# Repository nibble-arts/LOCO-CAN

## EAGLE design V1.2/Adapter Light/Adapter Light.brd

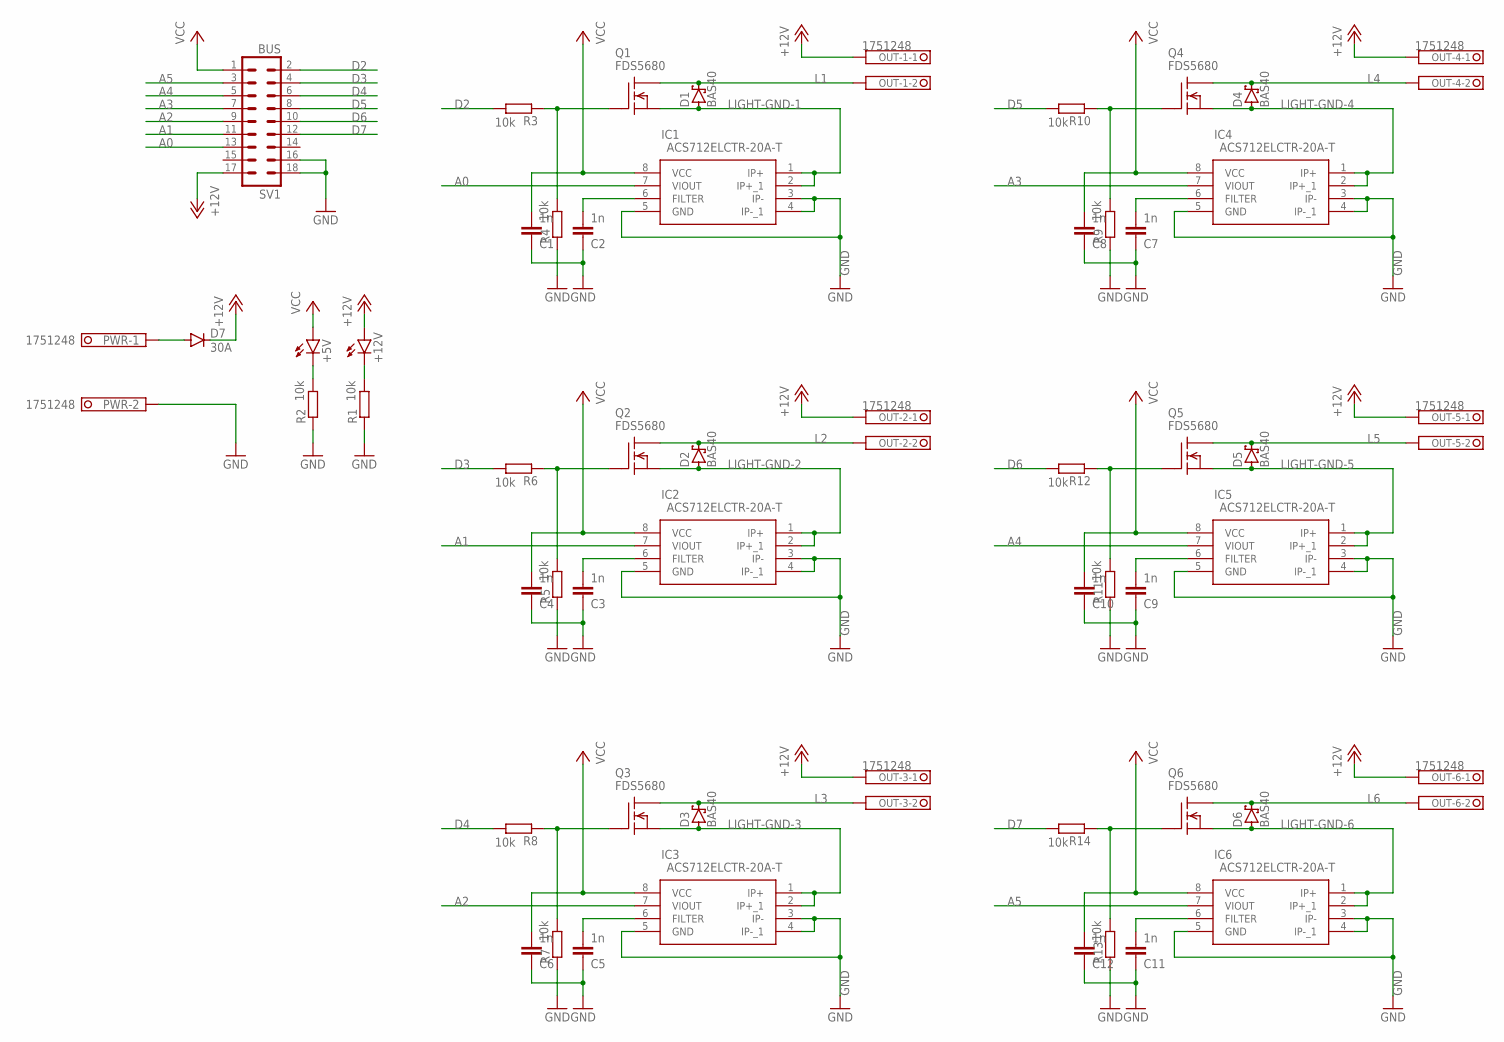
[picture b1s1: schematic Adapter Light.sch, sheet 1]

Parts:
+5V, +12V: LED3MM
C1, C2, C3, C4, C5, C6, C7, C8, C9, C10, C11, C12: 1n; C0402K
D1, D2, D3, D4, D5, D6: BAS40; SOT23
D7: 30A; DO15-12
IC1, IC2, IC3, IC4, IC5, IC6: ACS712ELCTR-20A-T; SOIC127P600X175-8N
OUT-1, OUT-2, OUT-3, OUT-4, OUT-5, OUT-6: 1751248
PWR: 1751248
Q1, Q2, Q3, Q4, Q5, Q6: FDS5680; SO-8
R1, R2, R3, R4, R5, R6, R7, R8, R9, R10, R11, R12, R13, R14: 10k; MINI_MELF-0102W
SV1: BUS; MA09-2

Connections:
+12V: +12V.A, D7.C, OUT-1.1, OUT-2.1, OUT-3.1, OUT-4.1, OUT-5.1, OUT-6.1, SV1.17
A0: IC1.7 (VIOUT), SV1.13
A1: IC2.7 (VIOUT), SV1.11
A2: IC3.7 (VIOUT), SV1.9
A3: IC4.7 (VIOUT), SV1.7
A4: IC5.7 (VIOUT), SV1.5
A5: IC6.7 (VIOUT), SV1.3
D2: R3.2, SV1.2
D3: R6.2, SV1.4
D4: R8.2, SV1.6
D5: R10.2, SV1.8
D6: R12.2, SV1.10
D7: R14.2, SV1.12
GND: C1.1, C2.1, C3.1, C4.1, C5.1, C6.1, C7.1, C8.1, C9.1, C10.1, C11.1, C12.1, IC1.3 (IP-), IC1.4 (IP-_1), IC1.5 (GND), IC2.3 (IP-), IC2.4 (IP-_1), IC2.5 (GND), IC3.3 (IP-), IC3.4 (IP-_1), IC3.5 (GND), IC4.3 (IP-), IC4.4 (IP-_1), IC4.5 (GND), IC5.3 (IP-), IC5.4 (IP-_1), IC5.5 (GND), IC6.3 (IP-), IC6.4 (IP-_1), IC6.5 (GND), PWR.2, R1.1, R2.1, R4.1, R5.1, R7.1, R9.1, R11.1, R13.1, SV1.16, SV1.18
L1: D1.3 (C), OUT-1.2, Q1.5 (D), Q1.6 (D), Q1.7 (D), Q1.8 (D)
L2: D2.3 (C), OUT-2.2, Q2.5 (D), Q2.6 (D), Q2.7 (D), Q2.8 (D)
L3: D3.3 (C), OUT-3.2, Q3.5 (D), Q3.6 (D), Q3.7 (D), Q3.8 (D)
L4: D4.3 (C), OUT-4.2, Q4.5 (D), Q4.6 (D), Q4.7 (D), Q4.8 (D)
L5: D5.3 (C), OUT-5.2, Q5.5 (D), Q5.6 (D), Q5.7 (D), Q5.8 (D)
L6: D6.3 (C), OUT-6.2, Q6.5 (D), Q6.6 (D), Q6.7 (D), Q6.8 (D)
LIGHT-GND-1: D1.1 (A), IC1.1 (IP+), IC1.2 (IP+_1), Q1.1 (S), Q1.2 (S), Q1.3 (S)
LIGHT-GND-2: D2.1 (A), IC2.1 (IP+), IC2.2 (IP+_1), Q2.1 (S), Q2.2 (S), Q2.3 (S)
LIGHT-GND-3: D3.1 (A), IC3.1 (IP+), IC3.2 (IP+_1), Q3.1 (S), Q3.2 (S), Q3.3 (S)
LIGHT-GND-4: D4.1 (A), IC4.1 (IP+), IC4.2 (IP+_1), Q4.1 (S), Q4.2 (S), Q4.3 (S)
LIGHT-GND-5: D5.1 (A), IC5.1 (IP+), IC5.2 (IP+_1), Q5.1 (S), Q5.2 (S), Q5.3 (S)
LIGHT-GND-6: D6.1 (A), IC6.1 (IP+), IC6.2 (IP+_1), Q6.1 (S), Q6.2 (S), Q6.3 (S)
unnamed: C2.2, IC1.6 (FILTER)
unnamed: C3.2, IC2.6 (FILTER)
unnamed: Q2.4 (G), R5.2, R6.1
unnamed: C5.2, IC3.6 (FILTER)
unnamed: Q3.4 (G), R7.2, R8.1
unnamed: +12V.K (C), R1.2
unnamed: C7.2, IC4.6 (FILTER)
unnamed: Q4.4 (G), R9.2, R10.1
unnamed: Q1.4 (G), R3.1, R4.2
unnamed: C9.2, IC5.6 (FILTER)
unnamed: Q5.4 (G), R11.2, R12.1
unnamed: +5V.K (C), R2.2
unnamed: C11.2, IC6.6 (FILTER)
unnamed: Q6.4 (G), R13.2, R14.1
unnamed: D7.A, PWR.1
VCC: +5V.A, C1.2, C4.2, C6.2, C8.2, C10.2, C12.2, IC1.8 (VCC), IC2.8 (VCC), IC3.8 (VCC), IC4.8 (VCC), IC5.8 (VCC), IC6.8 (VCC), SV1.1

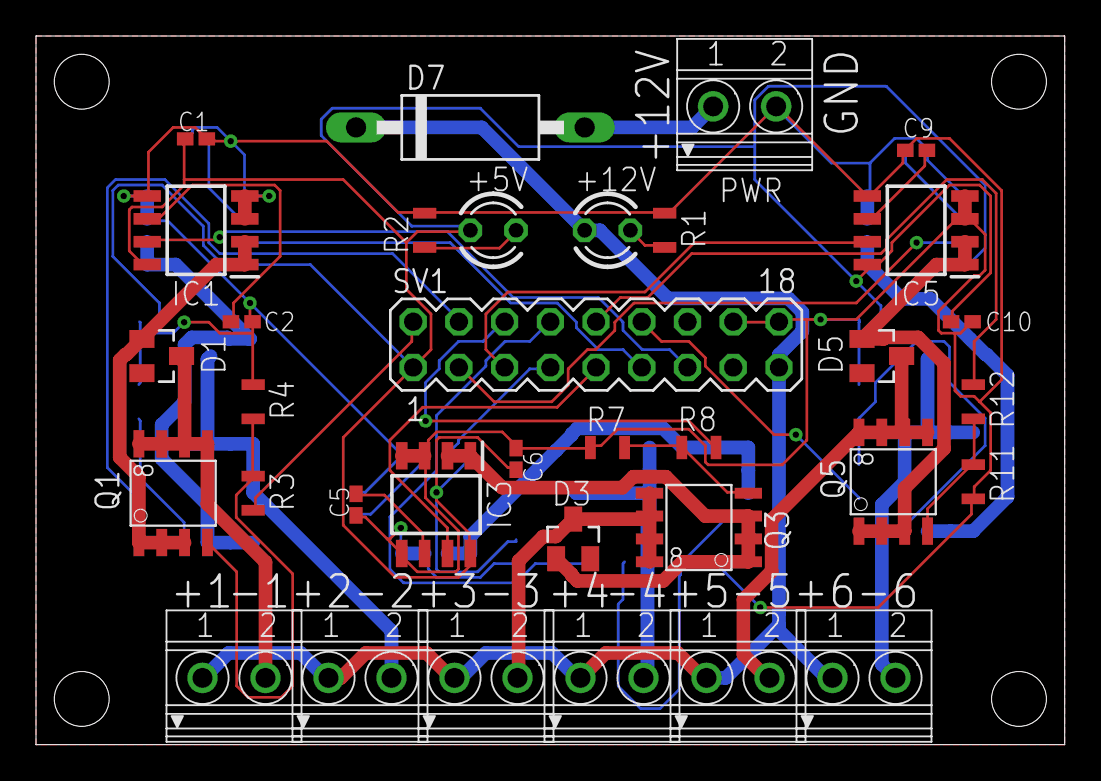
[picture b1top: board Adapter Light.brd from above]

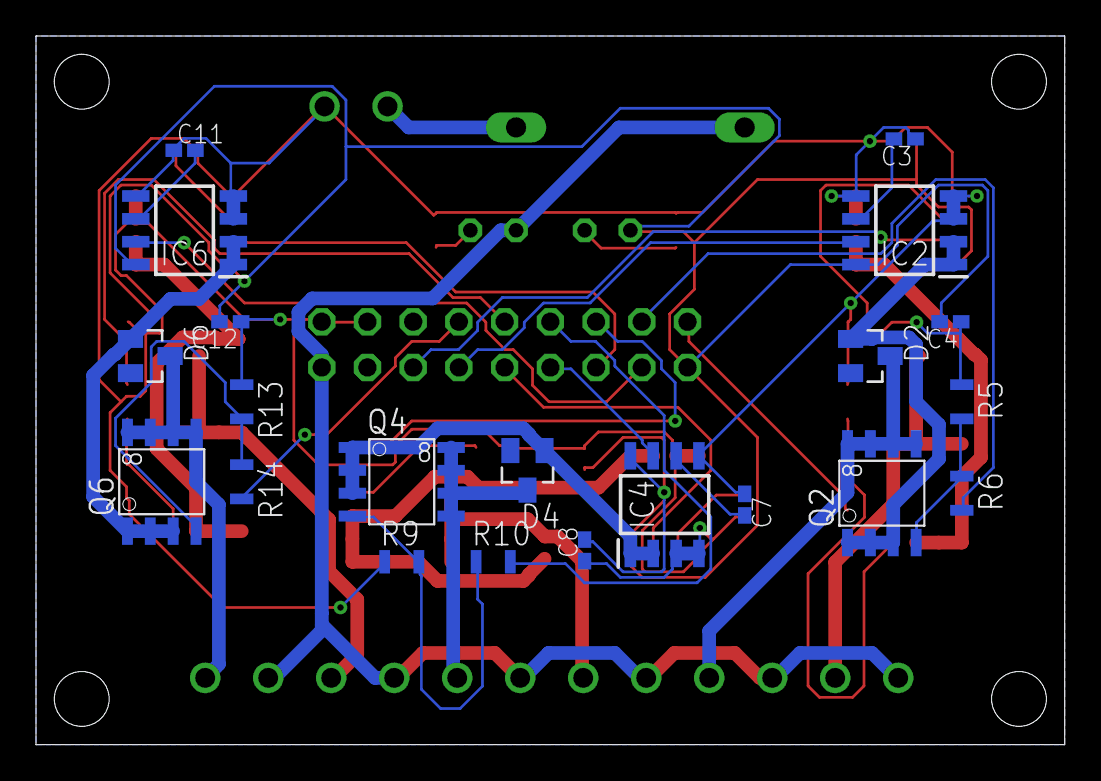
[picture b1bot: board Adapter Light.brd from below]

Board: 2 copper layers, 57.1 x 39.4 mm, 55 parts (21 on the bottom side), 42 nets.

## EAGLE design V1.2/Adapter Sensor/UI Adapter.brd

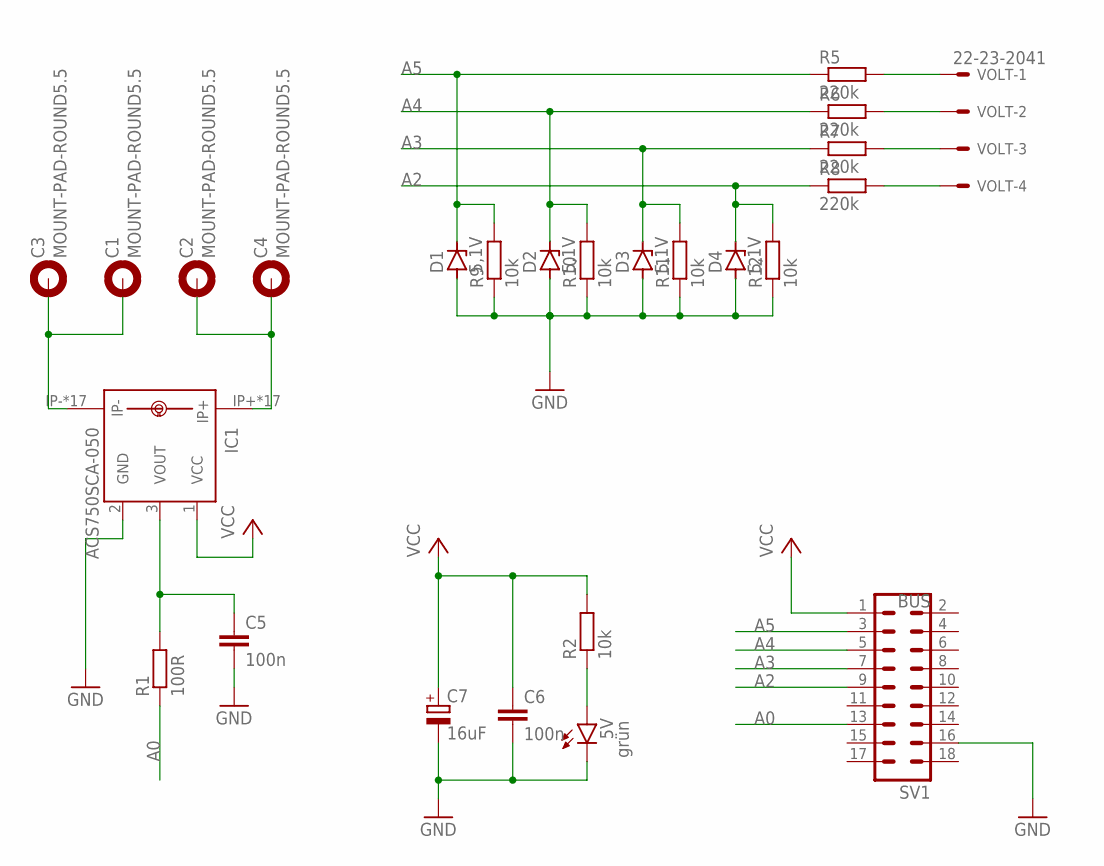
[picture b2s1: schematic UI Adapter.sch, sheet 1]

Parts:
5V: grün; LED3MM
C1, C2, C3, C4: MOUNT-PAD-ROUND5.5; 5,5-PAD
C5, C6: 100n; C025-024X044
C7: 16uF; E2-5
D1, D2, D3, D4: 5,1V; ZDIO-7.5
IC1: ACS750SCA-050; ACS75050
R1: 100R; 0204V
R2, R9, R10, R11, R12: 10k; 0204V
R5, R6, R7, R8: 220k; 0204V
SV1: BUS; MA09-2
VOLT: 22-23-2041

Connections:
A0: R1.1, SV1.13
A2: D4.C, R8.1, R12.2, SV1.9
A3: D3.C, R7.1, R11.2, SV1.7
A4: D2.C, R6.1, R10.2, SV1.5
A5: D1.C, R5.1, R9.2, SV1.3
C1: C1.B5,5, C3.B5,5, IC1.IP-, IC1.IP-@2 (IP-), IC1.IP-@3 (IP-), IC1.IP-@4 (IP-), IC1.IP-@5 (IP-), IC1.IP-@6 (IP-), IC1.IP-@7 (IP-), IC1.IP-@8 (IP-), IC1.IP-@9 (IP-), IC1.IP-@10 (IP-), IC1.IP-@11 (IP-), IC1.IP-@12 (IP-), IC1.IP-@13 (IP-), IC1.IP-@14 (IP-), IC1.IP-@15 (IP-), IC1.IP-@16 (IP-), IC1.IP-@17 (IP-)
C2: C2.B5,5, C4.B5,5, IC1.IP+, IC1.IP+@2 (IP+), IC1.IP+@3 (IP+), IC1.IP+@4 (IP+), IC1.IP+@5 (IP+), IC1.IP+@6 (IP+), IC1.IP+@7 (IP+), IC1.IP+@8 (IP+), IC1.IP+@9 (IP+), IC1.IP+@10 (IP+), IC1.IP+@11 (IP+), IC1.IP+@12 (IP+), IC1.IP+@13 (IP+), IC1.IP+@14 (IP+), IC1.IP+@15 (IP+), IC1.IP+@16 (IP+), IC1.IP+@17 (IP+)
GND: 5V.K (C), C5.2, C6.2, C7.-, D1.A, D2.A, D3.A, D4.A, IC1.2 (GND), R9.1, R10.1, R11.1, R12.1, SV1.16
unnamed: 5V.A, R2.1
unnamed: C5.1, IC1.3 (VOUT), R1.2
unnamed: R5.2, VOLT.1
unnamed: R6.2, VOLT.2
unnamed: R7.2, VOLT.3
unnamed: R8.2, VOLT.4
VCC: C6.1, C7.+, IC1.1 (VCC), R2.2, SV1.1

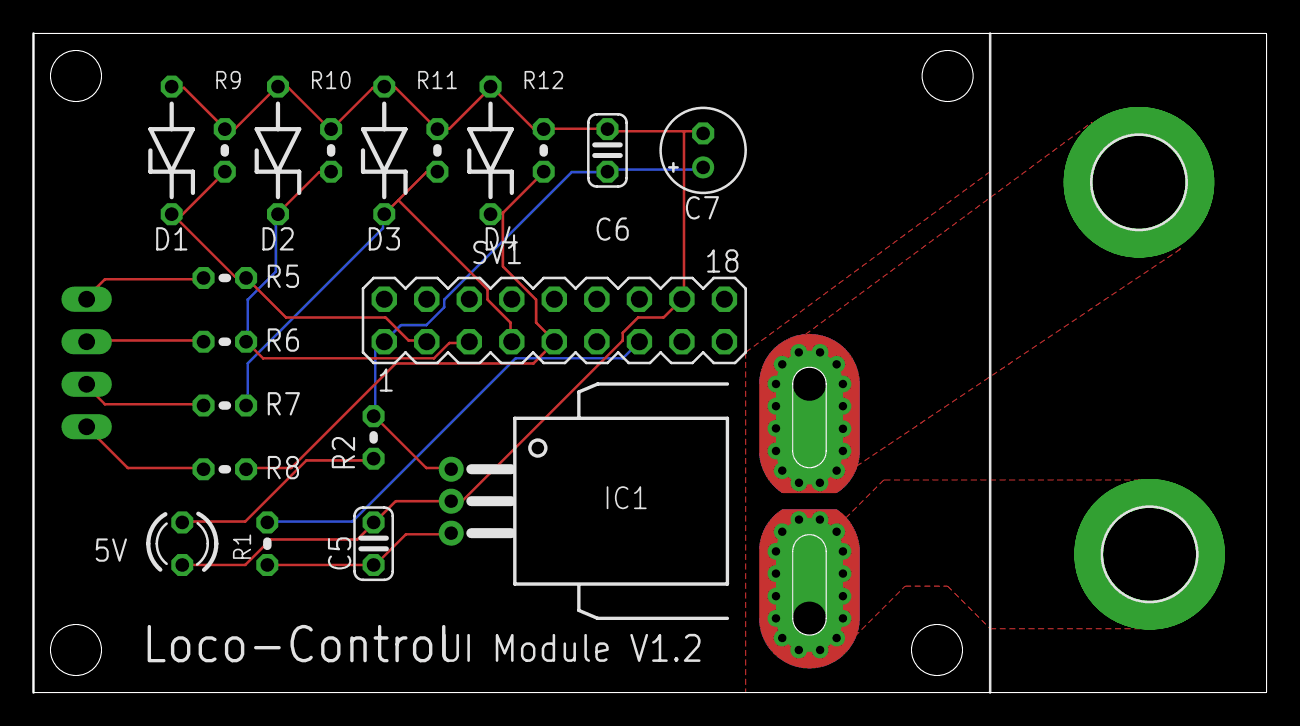
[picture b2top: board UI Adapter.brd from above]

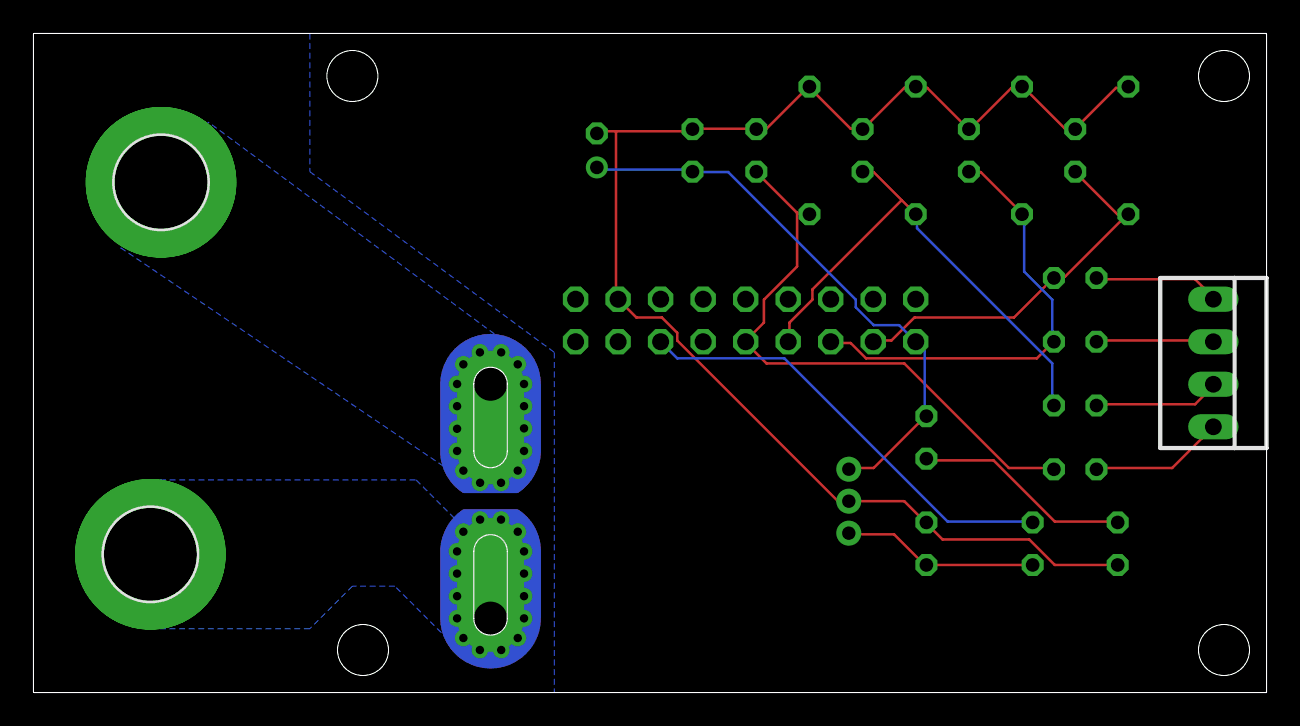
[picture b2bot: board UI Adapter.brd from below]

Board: 2 copper layers, 73.7 x 39.4 mm, 25 parts (3 on the bottom side), 15 nets.

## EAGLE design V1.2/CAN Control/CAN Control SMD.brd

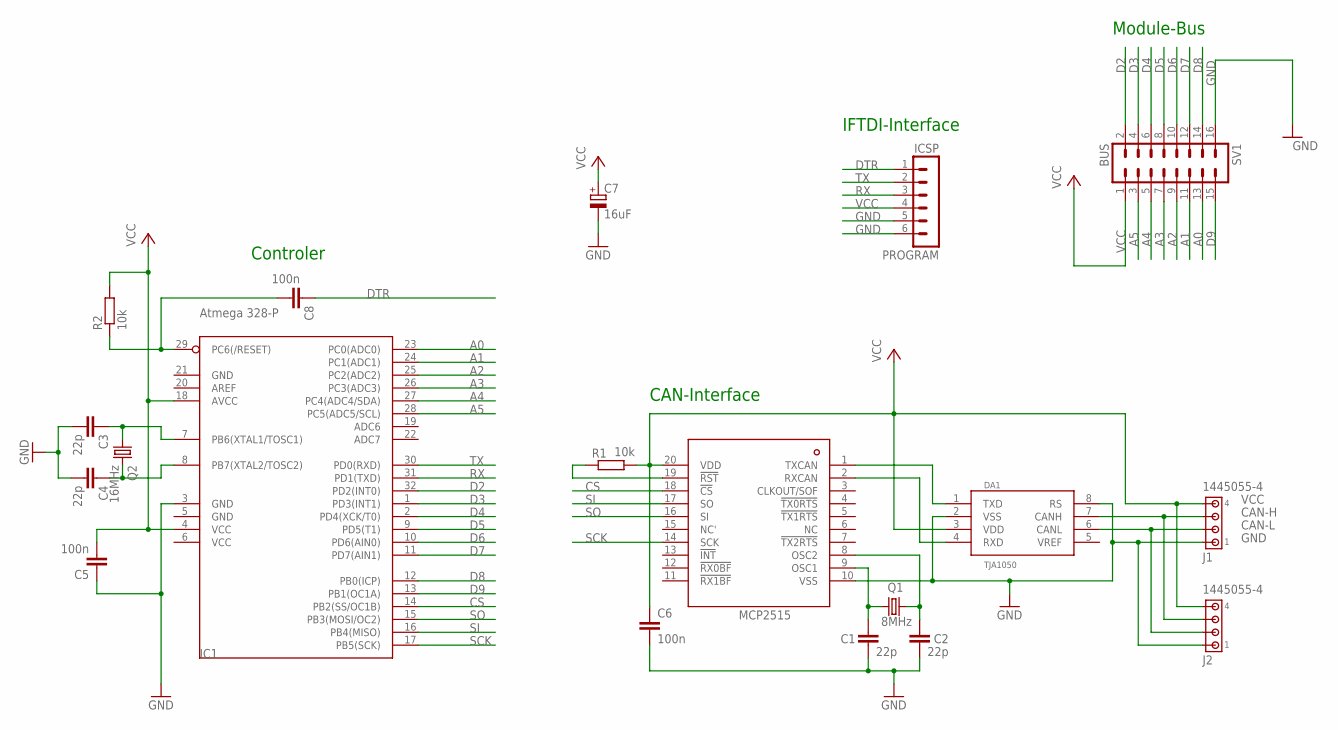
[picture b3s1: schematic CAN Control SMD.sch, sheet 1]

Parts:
C1, C2, C3, C4: 22p; C0402K
C5, C6, C8: 100n; C0402K
C7: 16uF; A/3216-18W
DA1: TJA1050; SO08
IC1: Atmega 328-P; TQFP32-08
IC2: MCP2515; TSSOP20
J1, J2: 1445055-4
PROGRAM: ICSP; MA06-1
Q1: 8MHz; HC49/S
Q2: 16MHz; HC49/S
R1, R2: 10k; MINI_MELF-0102W
SV1: BUS; MA08-2

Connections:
A0: IC1.23 (PC0(ADC0)), SV1.13
A1: IC1.24 (PC1(ADC1)), SV1.11
A2: IC1.25 (PC2(ADC2)), SV1.9
A3: IC1.26 (PC3(ADC3)), SV1.7
A4: IC1.27 (PC4(ADC4/SDA)), SV1.5
A5: IC1.28 (PC5(ADC5/SCL)), SV1.3
CAN-H: DA1.7 (CANH), J1.3, J2.3
CAN-L: DA1.6 (CANL), J1.2, J2.2
CAN-OCC1: C1.1, IC2.9 (OSC1), Q1.1
CAN-OCC2: C2.1, IC2.8 (OSC2), Q1.2
CS: IC1.14 (PB2(SS/OC1B)), IC2.18 (!CS)
D2: IC1.32 (PD2(INT0)), SV1.2
D3: IC1.1 (PD3(INT1)), SV1.4
D4: IC1.2 (PD4(XCK/T0)), SV1.6
D5: IC1.9 (PD5(T1)), SV1.8
D6: IC1.10 (PD6(AIN0)), SV1.10
D7: IC1.11 (PD7(AIN1)), SV1.12
D8: IC1.12 (PB0(ICP)), SV1.14
D9: IC1.13 (PB1(OC1A)), SV1.15
DTR: C8.1, PROGRAM.1
GND: C1.2, C2.2, C3.2, C4.2, C5.1, C6.2, C7.-, DA1.2 (VSS), DA1.8 (RS), IC1.3 (GND), IC1.5 (GND), IC1.21 (GND), IC2.10 (VSS), J1.1, J2.1, PROGRAM.5, PROGRAM.6, SV1.16
unnamed: IC2.19 (!RST), R1.1
unnamed: C3.1, IC1.7 (PB6(XTAL1/TOSC1)), Q2.1
unnamed: C4.1, IC1.8 (PB7(XTAL2/TOSC2)), Q2.2
unnamed: C8.2, IC1.29 (PC6(/RESET)), R2.1
RX: IC1.31 (PD1(TXD)), PROGRAM.3
RXCAN: DA1.4 (RXD), IC2.2 (RXCAN)
SCK: IC1.17 (PB5(SCK)), IC2.14 (SCK)
SI: IC1.16 (PB4(MISO)), IC2.17 (SO)
SO: IC1.15 (PB3(MOSI/OC2)), IC2.16 (SI)
TX: IC1.30 (PD0(RXD)), PROGRAM.2
TXCAN: DA1.1 (TXD), IC2.1 (TXCAN)
VCC: C5.2, C6.1, C7.+, DA1.3 (VDD), IC1.4 (VCC), IC1.6 (VCC), IC1.18 (AVCC), IC2.20 (VDD), J1.4, J2.4, PROGRAM.4, R1.2, R2.2, SV1.1

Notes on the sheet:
Module-Bus
IFTDI-Interface
CAN-Interface
Controler

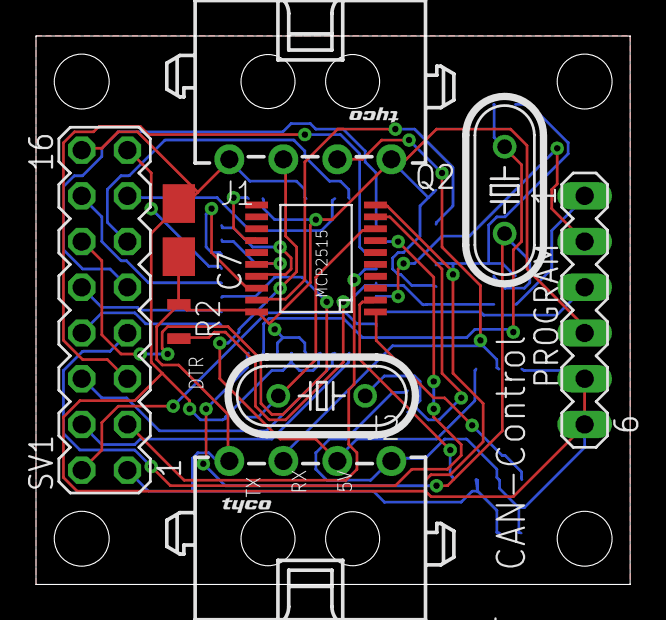
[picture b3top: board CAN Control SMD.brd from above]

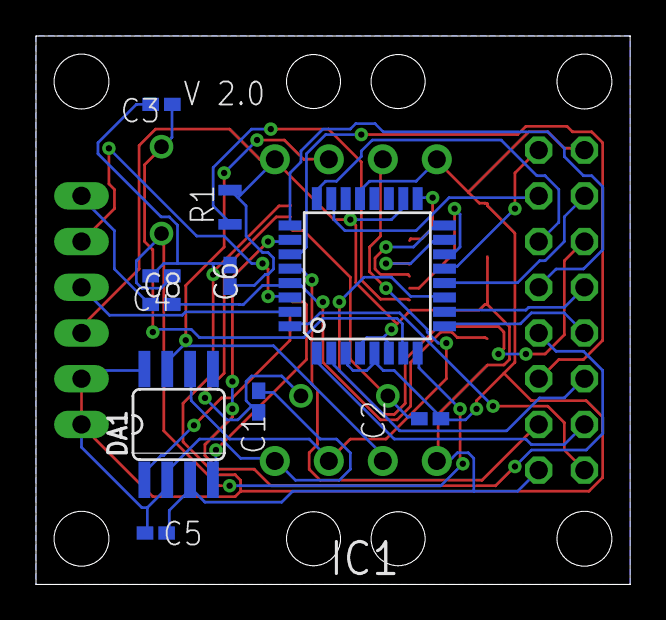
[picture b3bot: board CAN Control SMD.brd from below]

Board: 2 copper layers, 33.0 x 30.5 mm, 19 parts (10 on the bottom side), 33 nets.

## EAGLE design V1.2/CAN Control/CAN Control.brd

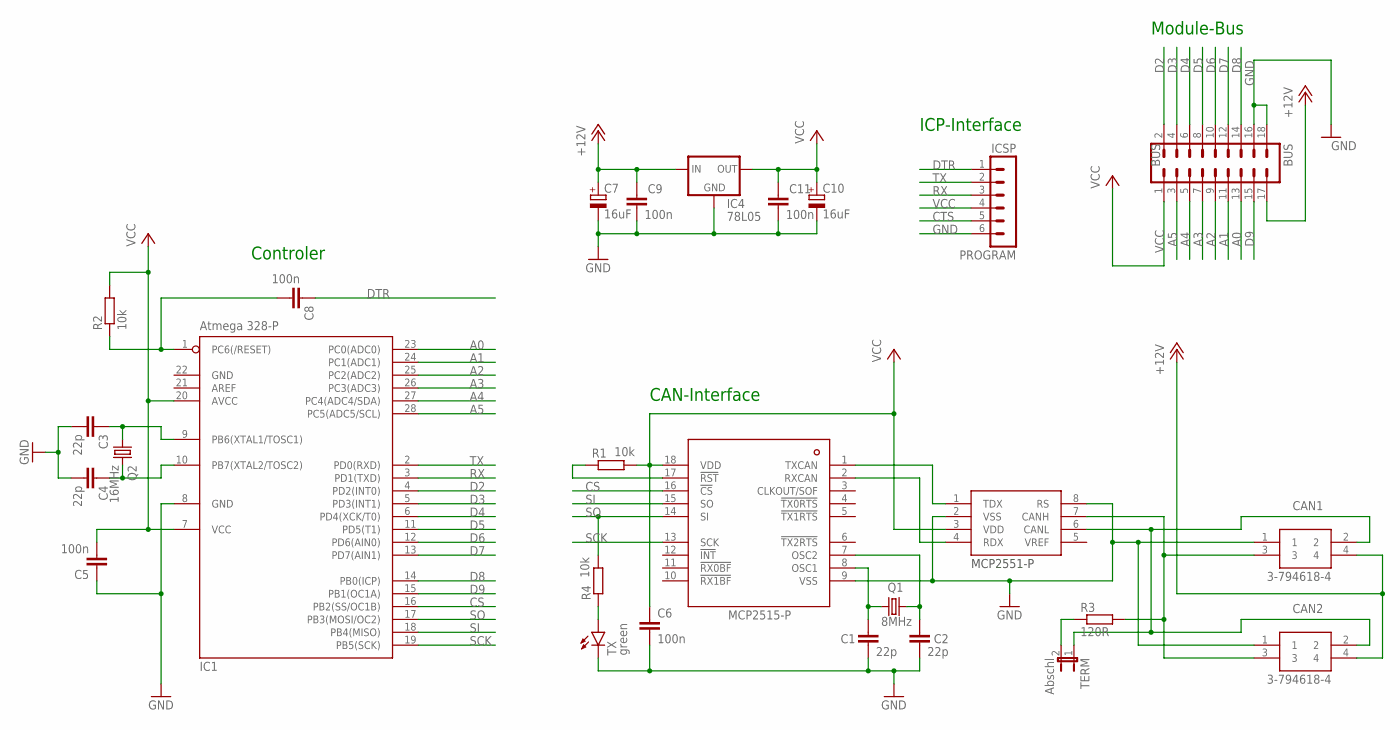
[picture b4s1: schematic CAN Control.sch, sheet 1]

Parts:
BUS: BUS; MA09-2
C1, C2, C3, C4: 22p; C025-024X044
C5, C6, C8, C9, C11: 100n; C025-024X044
C7, C10: 16uF; E2-5
CAN1, CAN2: 3-794618-4; SHDRRA4W102P300_2X2_686X892X73
IC1: Atmega 328-P; DIL28-3
IC2: MCP2515-P; DIL18
IC3: MCP2551-P; DIL8
IC4: 78L05; 78LXX
PROGRAM: ICSP; MA06-1
Q1: 8MHz; HC49/S
Q2: 16MHz; HC49/S
R1, R2, R4: 10k; 0204V
R3: 120R; 0204V
TERM: Abschl; JP1
TX: green; LED3MM

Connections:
+12V: BUS.17, C7.+, C9.1, CAN1.4, CAN2.4, IC4.IN
A0: BUS.13, IC1.23 (PC0(ADC0))
A1: BUS.11, IC1.24 (PC1(ADC1))
A2: BUS.9, IC1.25 (PC2(ADC2))
A3: BUS.7, IC1.26 (PC3(ADC3))
A4: BUS.5, IC1.27 (PC4(ADC4/SDA))
A5: BUS.3, IC1.28 (PC5(ADC5/SCL))
CAN2: CAN1.2, CAN2.2, IC3.6 (CANL), TERM.1
CAN-H: CAN1.3, CAN2.3, IC3.7 (CANH), R3.2
CAN-OCC1: C1.1, IC2.8 (OSC1), Q1.1
CAN-OCC2: C2.1, IC2.7 (OSC2), Q1.2
CS: IC1.16 (PB2(SS/OC1B)), IC2.16 (!CS)
CTS: PROGRAM.5
D2: BUS.2, IC1.4 (PD2(INT0))
D3: BUS.4, IC1.5 (PD3(INT1))
D4: BUS.6, IC1.6 (PD4(XCK/T0))
D5: BUS.8, IC1.11 (PD5(T1))
D6: BUS.10, IC1.12 (PD6(AIN0))
D7: BUS.12, IC1.13 (PD7(AIN1))
D8: BUS.14, IC1.14 (PB0(ICP))
D9: BUS.15, IC1.15 (PB1(OC1A))
DTR: C8.1, PROGRAM.1
GND: BUS.16, BUS.18, C1.2, C2.2, C3.2, C4.2, C5.1, C6.2, C7.-, C9.2, C10.-, C11.2, CAN1.1, CAN2.1, IC1.8 (GND), IC1.22 (GND), IC2.9 (VSS), IC3.2 (VSS), IC3.8 (RS), IC4.GND, PROGRAM.6, TX.K (C)
unnamed: R4.1, TX.A
unnamed: IC2.17 (!RST), R1.1
unnamed: C3.1, IC1.9 (PB6(XTAL1/TOSC1)), Q2.1
unnamed: C4.1, IC1.10 (PB7(XTAL2/TOSC2)), Q2.2
unnamed: R3.1, TERM.2
unnamed: C8.2, IC1.1 (PC6(/RESET)), R2.1
RX: IC1.3 (PD1(TXD)), PROGRAM.3
RXCAN: IC2.2 (RXCAN), IC3.4 (RDX)
SCK: IC1.19 (PB5(SCK)), IC2.13 (SCK)
SI: IC1.18 (PB4(MISO)), IC2.15 (SO)
SO: IC1.17 (PB3(MOSI/OC2)), IC2.14 (SI), R4.2
TX: IC1.2 (PD0(RXD)), PROGRAM.2
TXCAN: IC2.1 (TXCAN), IC3.1 (TDX)
VCC: BUS.1, C5.2, C6.1, C10.+, C11.1, IC1.7 (VCC), IC1.20 (AVCC), IC2.18 (VDD), IC3.3 (VDD), IC4.OUT, PROGRAM.4, R1.2, R2.2

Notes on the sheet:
Module-Bus
ICP-Interface
CAN-Interface
Controler

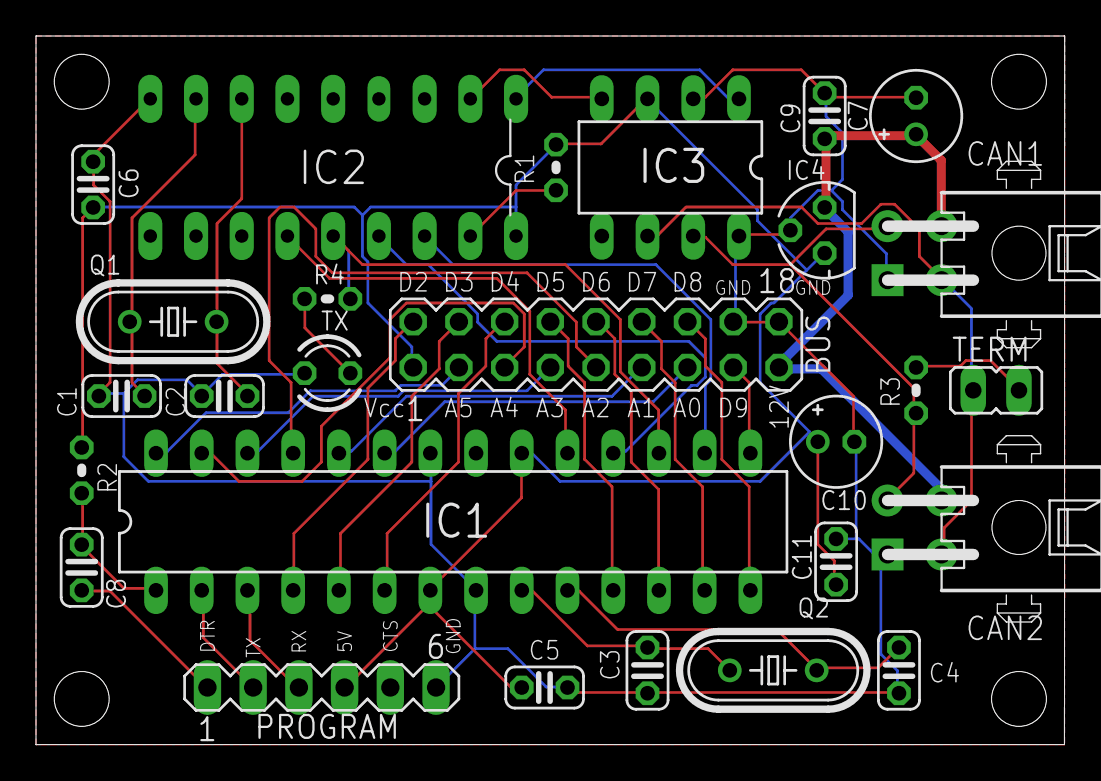
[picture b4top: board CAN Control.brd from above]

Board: 2 copper layers, 57.1 x 39.4 mm, 27 parts (0 on the bottom side), 36 nets.

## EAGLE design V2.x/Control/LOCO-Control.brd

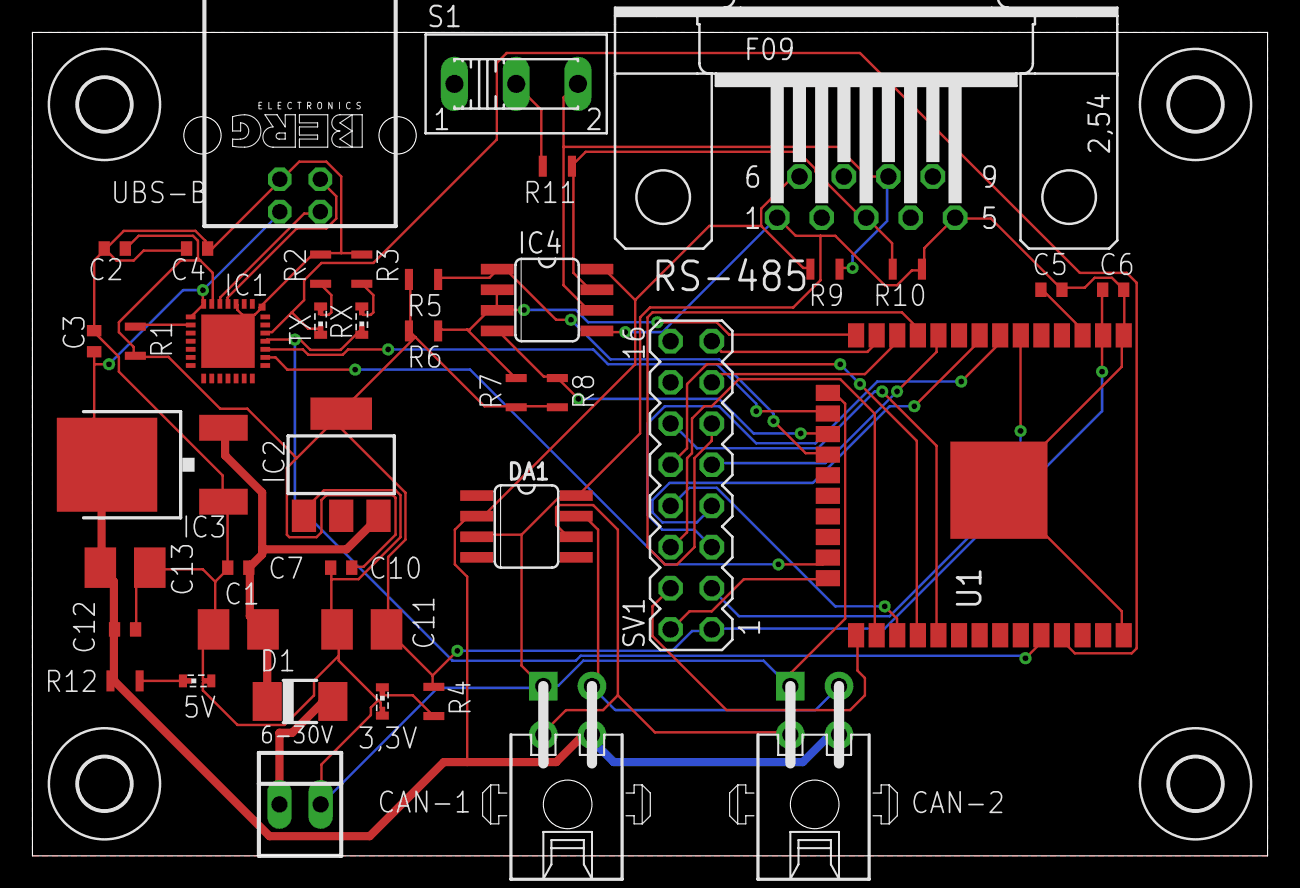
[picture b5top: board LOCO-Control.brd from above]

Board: 2 copper layers, 76.2 x 50.8 mm, 45 parts (0 on the bottom side), 38 nets.

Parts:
3,3V, 5V: SMARTLED-TTW
6-30V: 22-23-2021
C1, C11, C13: 47uF; B/3528-21R
C2, C4: 104; C0402
C3: 47uF; C0402
C5: 1uF; C0402
C6: 100n; C0402
C7, C10, C12: 100nF; C0402
CAN-1, CAN-2: 3-794618-4; SHDRRA4W102P300_2X2_686X892X73
D1: DO-214AC
DA1: TJA1050; SO08
IC1: CP2102; MLP28
IC2: LD117AS33TR; SOT223
IC3: LD117ADT50TR; DPACK
IC4: MAX3468CSA; SO08
R1: 5k; MINI_MELF-0102R
R2, R3: 330R; MINI_MELF-0102R
R4, R5, R6, R7, R8, R12: 10K; MINI_MELF-0102R
R9, R10: 20K; MINI_MELF-0102R
R11: 120R; MINI_MELF-0102R
RS-485: F09H
RX: SMARTLED-TTW
S1: 255SB
SV1: MA08-2
TX: SMARTLED-TTW
U1: ESP-WROOM-32
U$2, U$3, U$4, U$5: 3,2
UBS-B: PN61729

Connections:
+3V3: C2.1, C6.1, C10.1, C11.+, IC1.6, IC2.4, R1.2, R4.2, R5.2, R6.2, R7.2, R8.2, SV1.1, U1.2
+5V: C3.1, C12.1, C13.+, CAN-1.4, CAN-2.4, DA1.2, IC1.7, IC1.8, IC3.4, IC4.8, R9.2, R12.2, RS-485.6, UBS-B.1
+12V: C1.+, C7.1, D1.C, IC2.3, IC3.3
CP-CTS: IC1.23, U1.23
CP-RDX: IC1.25, RX.A@1, U1.34
CP-RTS: IC1.24, U1.16
CP-TDX: IC1.26, TX.A@1, U1.35
GND: 3,3V.C@1, 5V.C@1, 6-30V.2, C1.-, C2.2, C3.2, C4.1, C4.2, C5.2, C6.2, C7.2, C10.2, C11.-, C12.2, C13.-, CAN-1.1, CAN-2.1, DA1.3, DA1.8, IC1.3, IC1.EXP, IC1.M, IC2.1, IC3.1, IC4.5, R2.2, R3.2, R10.1, RS-485.1, RS-485.5, SV1.16, U1.1, U1.15, U1.38, U1.GND, UBS-B.4
IO0: SV1.4, U1.25
IO2: SV1.2, U1.24
IO4: SV1.6, U1.26
IO5: SV1.12, U1.29
IO14: SV1.15, U1.13
IO16: SV1.8, U1.27
IO17: SV1.10, U1.28
IO25: SV1.9, U1.10
IO26: SV1.11, U1.11
IO27: SV1.13, U1.12
IO32: SV1.7, U1.8
IO34: SV1.3, U1.6
IO35: SV1.5, U1.7
unnamed: IC1.5, UBS-B.2
unnamed: IC1.4, UBS-B.3
unnamed: IC1.9, R1.1
unnamed: 6-30V.1, D1.A
unnamed: R2.1, TX.C@1
unnamed: 3,3V.A@1, R4.1
unnamed: R3.1, RX.C@1
unnamed: CAN-1.3, CAN-2.3, DA1.7
unnamed: CAN-1.2, CAN-2.2, DA1.6
unnamed: IC4.6, R9.1, RS-485.8, S1.3
unnamed: IC4.7, R10.2, R11.1, RS-485.3
unnamed: R11.2, S1.2
unnamed: 5V.A@1, R12.1
RDX1: IC4.4, R8.1, U1.17
RE/DE: IC4.2, IC4.3, R6.1, R7.1, U1.14
RESET: C5.1, U1.3
TDX1: IC4.1, R5.1, U1.18

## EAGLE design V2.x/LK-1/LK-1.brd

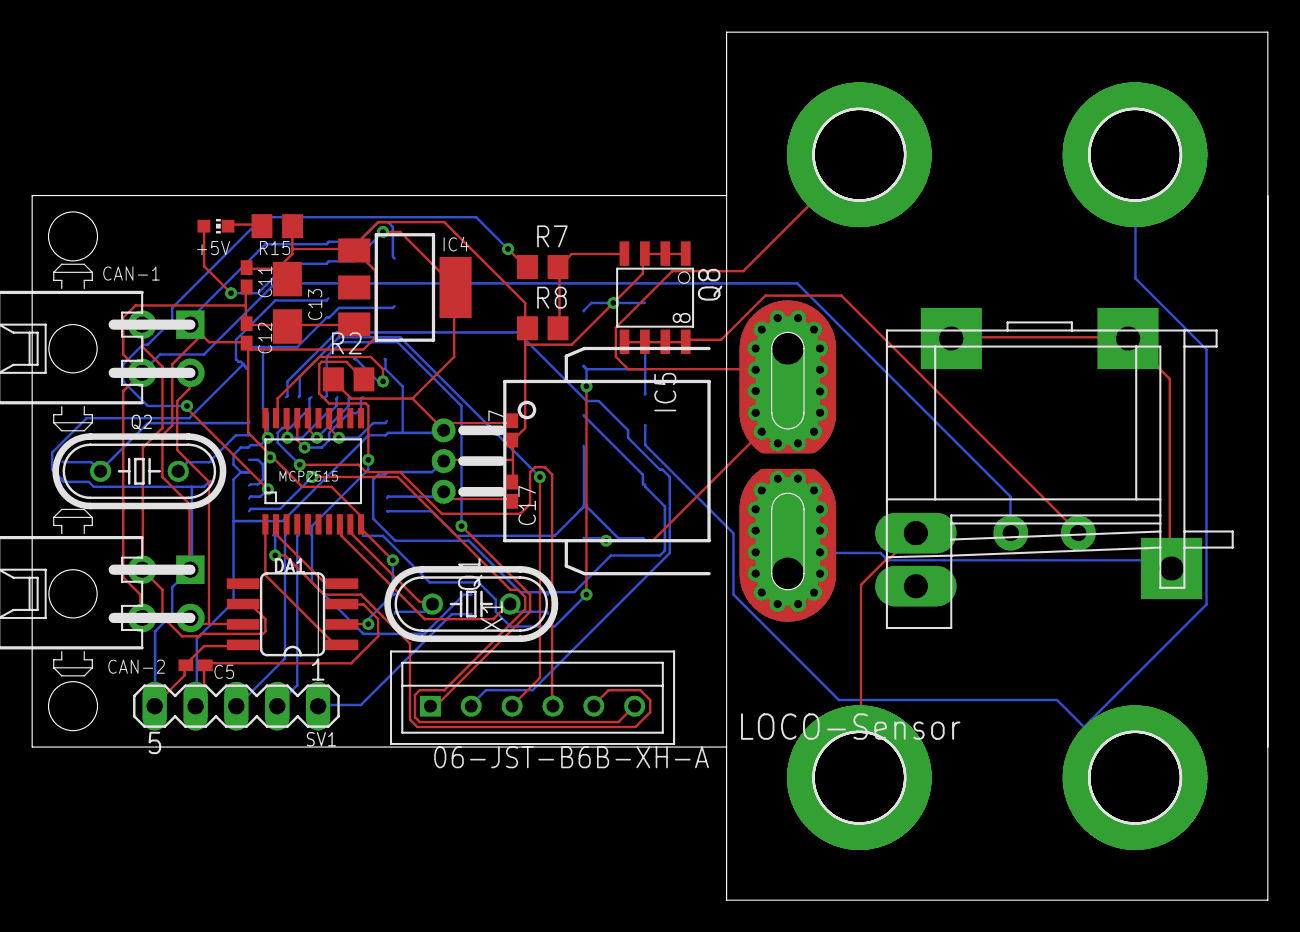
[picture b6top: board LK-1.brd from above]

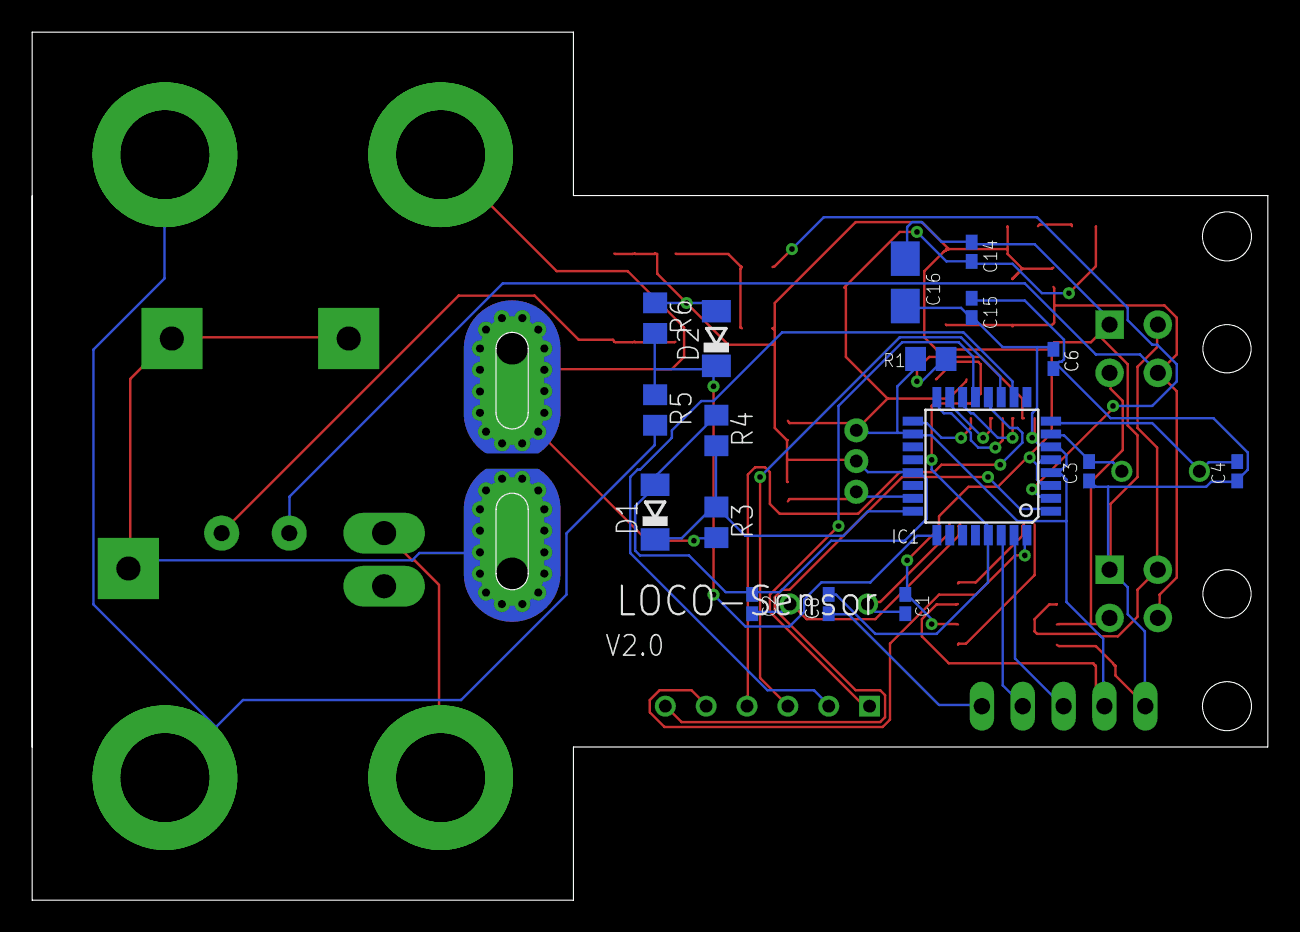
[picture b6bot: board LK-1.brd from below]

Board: 2 copper layers, 76.8 x 54.0 mm, 48 parts (17 on the bottom side), 37 nets.

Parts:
+5V: CHIP-LED0603
C1, C2, C3, C4: 22p; C0402K
C5, C6, C7, C8, C11, C15: 100n; C0402K
C12, C14, C17: 1n; C0402K
C13, C16: 16uF; A/3216-18W
C+BOT: PAD 5.5; 5,5-PAD
C+TOP: PAD 5.5; 5,5-PAD
C-BOT1: PAD 5.5; 5,5-PAD
C-TOP1: PAD 5.5; 5,5-PAD
CAN-1, CAN-2: 3-794618-4; SHDRRA4W102P300_2X2_686X892X73
D1, D2: SOD80C
DA1: TJA1050; SO08
IC1: Atmega 328-P; TQFP32-08
IC2: MCP2515; TSSOP20
IC4: LD117AS12TR; SOT223
IC5: ACS750LCA-050; ACS75050
M+-BOT: PAD 5.5; 5,5-PAD
M+-TOP: PAD 5.5; 5,5-PAD
M--BOT1: PAD 5.5; 5,5-PAD
M--TOP1: PAD 5.5; 5,5-PAD
Q1: 8MHz; HC49/S
Q2: 16MHz; HC49/S
Q8: FDS5680; SO-8
R1, R2, R4, R6, R7, R8, R15: 10k; R0805
R3, R5: 220K; R0805
SV1: MA05-1
U$1: FRA2C-2
X1: 06-JST-B6B-XH-A; B6B-XH

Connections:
+12V: C11.2, C12.2, C13.+, CAN-1.4, CAN-2.4, IC4.3, U$1.C2
A0: C17.2, IC1.23, IC5.3
A1: D1.C, IC1.24, R3.1, R4.2
A2: D2.C, IC1.25, R5.1, R6.2
C-: C+BOT.B5,5, C+TOP.B5,5, U$1.NO
C-1: IC5.IP+, IC5.IP+@2, IC5.IP+@3, IC5.IP+@4, IC5.IP+@5, IC5.IP+@6, IC5.IP+@7, IC5.IP+@8, IC5.IP+@9, IC5.IP+@10, IC5.IP+@11, IC5.IP+@12, IC5.IP+@13, IC5.IP+@14, IC5.IP+@15, IC5.IP+@16, IC5.IP+@17, U$1.COM1, U$1.COM2, U$1.COM3
CAN-H: CAN-1.3, CAN-2.3, DA1.7
CAN-L: CAN-1.2, CAN-2.2, DA1.6
CAN-OCC1: C1.1, IC2.9, Q1.1
CAN-OCC2: C2.1, IC2.8, Q1.2
CS: IC1.14, IC2.18
D2: IC1.32, X1.P$5
D3: IC1.1, X1.P$6
D4: IC1.2, R7.1
D6: IC1.10, X1.P$2
D7: IC1.11, X1.P$3
D8: IC1.12, X1.P$4
D9: IC1.13, X1.P$1
DTR: C8.1, SV1.1
GND: C1.2, C2.2, C3.2, C4.2, C5.1, C6.2, C7.1, C11.1, C12.1, C13.-, C14.1, C15.1, C16.-, C17.1, CAN-1.1, CAN-2.1, D1.A, D2.A, DA1.2, DA1.8, IC1.3, IC1.5, IC1.21, IC2.10, IC4.1, IC5.2, Q8.1, Q8.2, Q8.3, R4.1, R6.1, R8.1, R15.1, SV1.5
M+: IC5.IP-, IC5.IP-@2, IC5.IP-@3, IC5.IP-@4, IC5.IP-@5, IC5.IP-@6, IC5.IP-@7, IC5.IP-@8, IC5.IP-@9, IC5.IP-@10, IC5.IP-@11, IC5.IP-@12, IC5.IP-@13, IC5.IP-@14, IC5.IP-@15, IC5.IP-@16, IC5.IP-@17, M+-BOT.B5,5, M+-TOP.B5,5, R3.2
M-: C-BOT1.B5,5, C-TOP1.B5,5, M--BOT1.B5,5, M--TOP1.B5,5, R5.2
unnamed: Q8.5, Q8.6, Q8.7, Q8.8, U$1.C1
unnamed: Q8.4, R7.2, R8.2
unnamed: IC2.19, R1.1
unnamed: C3.1, IC1.7, Q2.1
unnamed: C4.1, IC1.8, Q2.2
unnamed: +5V.C, R15.2
unnamed: C8.2, IC1.29, R2.1
RX: IC1.31, SV1.3
RXCAN: DA1.4, IC2.2
SCK: IC1.17, IC2.14
SI: IC1.16, IC2.17
SO: IC1.15, IC2.16
TX: IC1.30, SV1.2
TXCAN: DA1.1, IC2.1
VCC: +5V.A, C5.2, C6.1, C7.2, C14.2, C15.2, C16.+, DA1.3, IC1.4, IC1.6, IC1.18, IC2.20, IC4.4, IC5.1, R1.2, R2.2, SV1.4

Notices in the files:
V1.2/CAN Control/CAN Control.brd:
V 1.2 - (c) 2020
parts and their libraries:
esp32: Creative Commons Attribution-ShareAlike 4.0 International
